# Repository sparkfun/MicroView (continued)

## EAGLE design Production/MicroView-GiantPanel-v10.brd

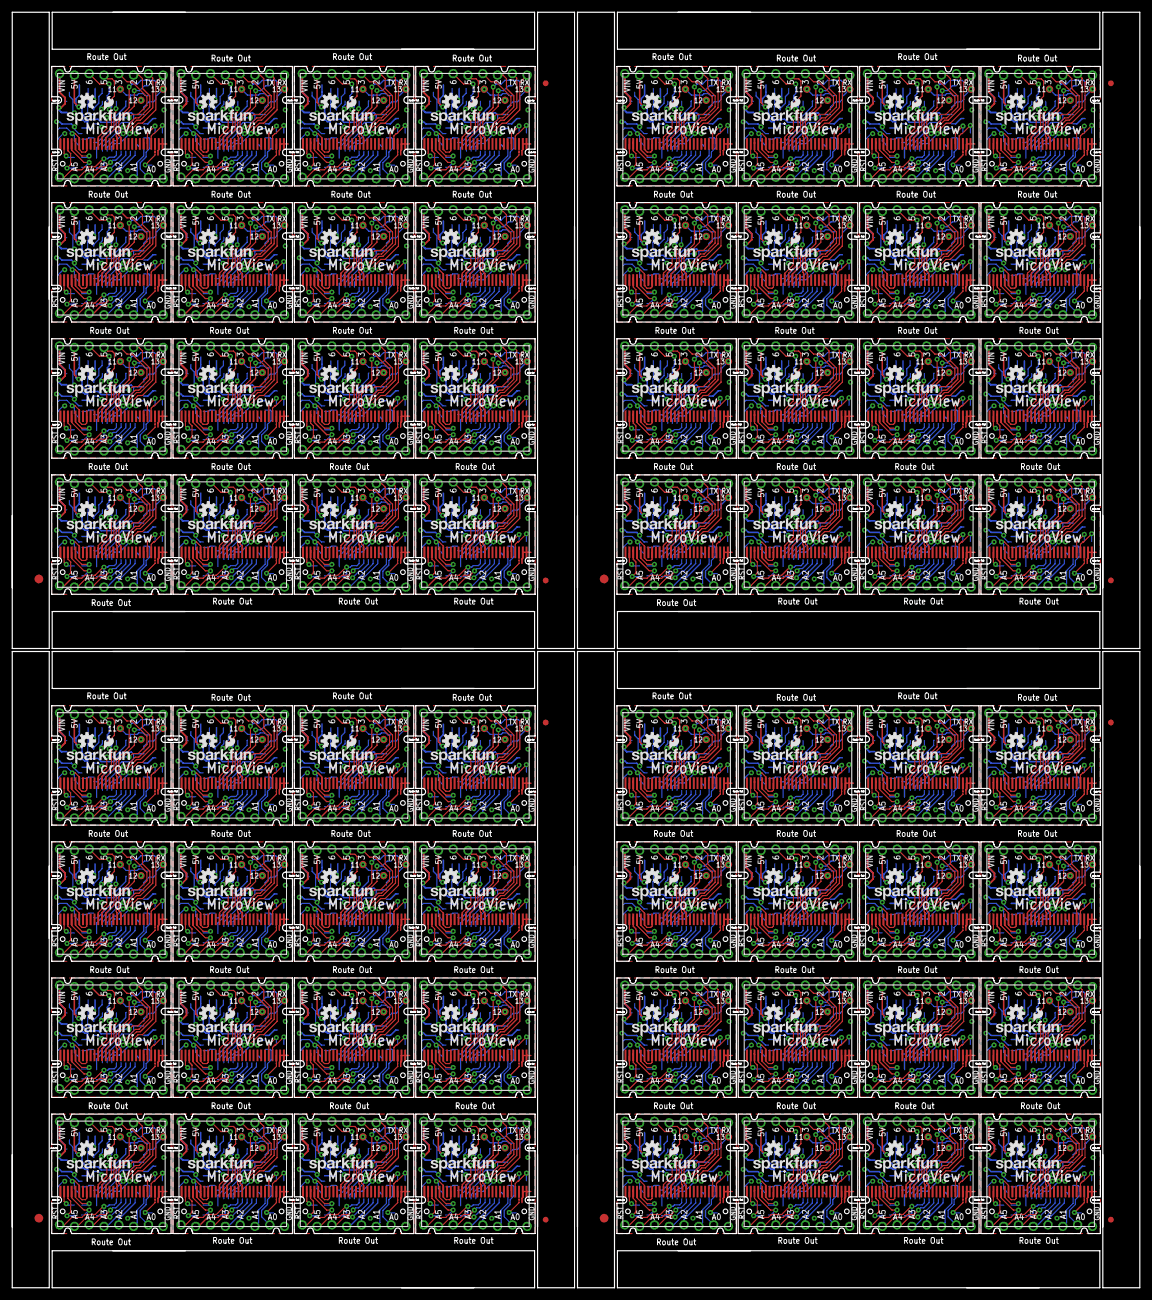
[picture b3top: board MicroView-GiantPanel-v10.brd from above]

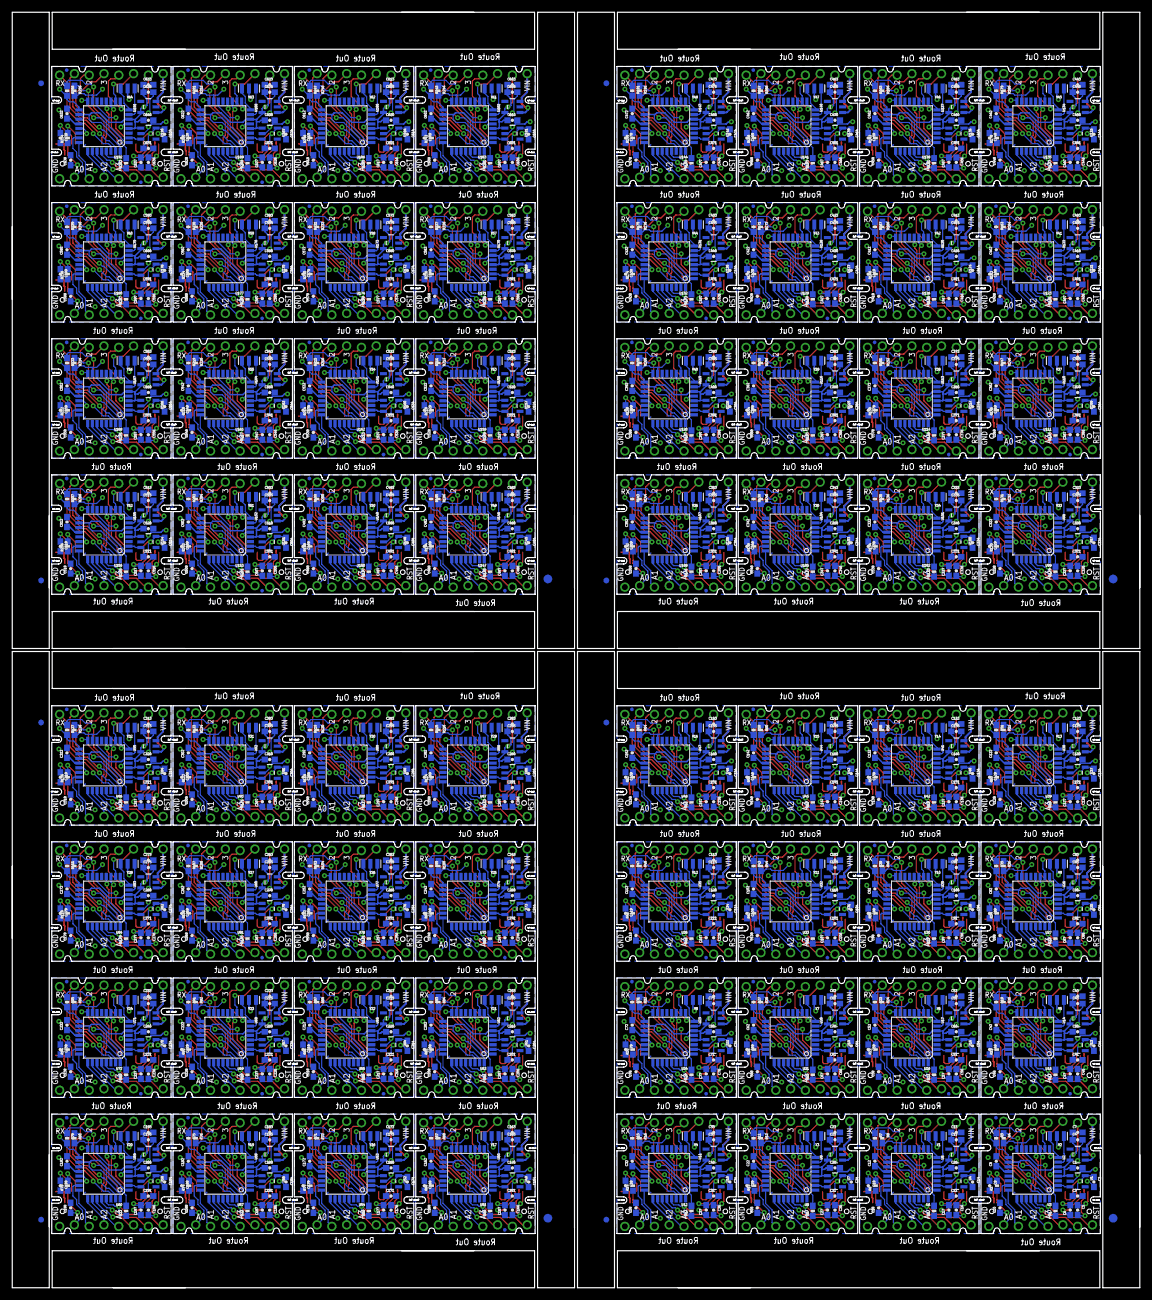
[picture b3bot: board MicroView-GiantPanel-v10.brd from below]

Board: 2 copper layers, 193.5 x 218.9 mm, 1816 parts (1292 on the bottom side), 2304 nets.

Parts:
C1, C2, C4, C5, C6, C14, C15, C16, C17, C20, C24, C25, C26, C27, C30, C34, C35, C36, C37, C40, C44, C45, C46, C47, C50, C54, C55, C56, C57, C60, C64, C65, C66, C67, C70, C74, C75, C76, C77, C80, C84, C85, C86, C87, C90, C94, C95, C96, C97, C100, C104, C105, C106, C107, C110, C114, C115, C116, C117, C120, C124, C125, C126, C127, C130, C134, C135, C136, C137, C140, C144, C145, C146, C147, C150, C154, C155, C156, C157, C160, C164, C165, C166, C167, C170, C174, C175, C176, C177, C180, C184, C185, C186, C187, C190, C194, C195, C196, C197, C200, C204, C205, C206, C207, C210, C214, C215, C216, C217, C220, C224, C225, C226, C227, C230, C234, C235, C236, C237, C240, C244, C245, C246, C247, C250, C254, C255, C256, C257, C260, C264, C265, C266, C267, C270, C274, C275, C276, C277, C280, C284, C285, C286, C287, C290, C294, C295, C296, C297, C300, C304, C305, C306, C307, C310, C314, C315, C316, C317, C320, C324, C325, C326, C327, C330, C334, C335, C336, C337, C340, C344, C345, C346, C347, C350, C354, C355, C356, C357, C360, C364, C365, C366, C367, C370, C374, C375, C376, C377, C380, C384, C385, C386, C387, C390, C394, C395, C396, C397, C400, C404, C405, C406, C407, C410, C414, C415, C416, C417, C420, C424, C425, C426, C427, C430, C434, C435, C436, C437, C440, C444, C445, C446, C447, C450, C454, C455, C456, C457, C460, C464, C465, C466, C467, C470, C474, C475, C476, C477, C480, C484, C485, C486, C487, C490, C494, C495, C496, C497, C500, C504, C505, C506, C507, C510, C514, C515, C516, C517, C520, C524, C525, C526, C527, C530, C534, C535, C536, C537, C540, C544, C545, C546, C547, C550, C554, C555, C556, C557, C560, C564, C565, C566, C567, C570, C574, C575, C576, C577, C580, C584, C585, C586, C587, C590, C594, C595, C596, C597, C600, C604, C605, C606, C607, C610, C614, C615, C616, C617, C620, C624, C625, C626, C627, C630, C634, C635, C636, C637, C640: 1.0uF; 0603-CAP
C3, C7, C8, C11, C12, C13, C21, C22, C23, C31, C32, C33, C41, C42, C43, C51, C52, C53, C61, C62, C63, C71, C72, C73, C81, C82, C83, C91, C92, C93, C101, C102, C103, C111, C112, C113, C121, C122, C123, C131, C132, C133, C141, C142, C143, C151, C152, C153, C161, C162, C163, C171, C172, C173, C181, C182, C183, C191, C192, C193, C201, C202, C203, C211, C212, C213, C221, C222, C223, C231, C232, C233, C241, C242, C243, C251, C252, C253, C261, C262, C263, C271, C272, C273, C281, C282, C283, C291, C292, C293, C301, C302, C303, C311, C312, C313, C321, C322, C323, C331, C332, C333, C341, C342, C343, C351, C352, C353, C361, C362, C363, C371, C372, C373, C381, C382, C383, C391, C392, C393, C401, C402, C403, C411, C412, C413, C421, C422, C423, C431, C432, C433, C441, C442, C443, C451, C452, C453, C461, C462, C463, C471, C472, C473, C481, C482, C483, C491, C492, C493, C501, C502, C503, C511, C512, C513, C521, C522, C523, C531, C532, C533, C541, C542, C543, C551, C552, C553, C561, C562, C563, C571, C572, C573, C581, C582, C583, C591, C592, C593, C601, C602, C603, C611, C612, C613, C621, C622, C623, C631, C632, C633: 0.1uF; 0603-CAP
C9, C10, C18, C19, C28, C29, C38, C39, C48, C49, C58, C59, C68, C69, C78, C79, C88, C89, C98, C99, C108, C109, C118, C119, C128, C129, C138, C139, C148, C149, C158, C159, C168, C169, C178, C179, C188, C189, C198, C199, C208, C209, C218, C219, C228, C229, C238, C239, C248, C249, C258, C259, C268, C269, C278, C279, C288, C289, C298, C299, C308, C309, C318, C319, C328, C329, C338, C339, C348, C349, C358, C359, C368, C369, C378, C379, C388, C389, C398, C399, C408, C409, C418, C419, C428, C429, C438, C439, C448, C449, C458, C459, C468, C469, C478, C479, C488, C489, C498, C499, C508, C509, C518, C519, C528, C529, C538, C539, C548, C549, C558, C559, C568, C569, C578, C579, C588, C589, C598, C599, C608, C609, C618, C619, C628, C629, C638, C639: 2.2uF; 0603-CAP
E$1, E$2, E$9, E$10, E$15, E$16, E$21, E$22: FIDUCIAL-1.5X3
E$3, E$4, E$5, E$6, E$7, E$8, E$11, E$12, E$13, E$14, E$17, E$18, E$19, E$20, E$23, E$24: FIDUCIAL-1X2
FID1, FID2, FID3, FID4, FID5, FID6, FID7, FID8, FID9, FID10, FID11, FID12, FID13, FID14, FID15, FID16, FID17, FID18, FID19, FID20, FID21, FID22, FID23, FID24, FID25, FID26, FID27, FID28, FID29, FID30, FID31, FID32, FID33, FID34, FID35, FID36, FID37, FID38, FID39, FID40, FID41, FID42, FID43, FID44, FID45, FID46, FID47, FID48, FID49, FID50, FID51, FID52, FID53, FID54, FID55, FID56, FID57, FID58, FID59, FID60, FID61, FID62, FID63, FID64, FID65, FID66, FID67, FID68, FID69, FID70, FID71, FID72, FID73, FID74, FID75, FID76, FID77, FID78, FID79, FID80, FID81, FID82, FID83, FID84, FID85, FID86, FID87, FID88, FID89, FID90, FID91, FID92, FID93, FID94, FID95, FID96, FID97, FID98, FID99, FID100, FID101, FID102, FID103, FID104, FID105, FID106, FID107, FID108, FID109, FID110, FID111, FID112, FID113, FID114, FID115, FID116, FID117, FID118, FID119, FID120, FID121, FID122, FID123, FID124, FID125, FID126, FID127, FID128: FIDUCIALUFIDUCIAL; MICRO-FIDUCIAL
J1, J4, J6, J8, J10, J12, J14, J16, J18, J20, J22, J24, J26, J28, J30, J32, J34, J36, J38, J40, J42, J44, J46, J48, J50, J52, J54, J56, J58, J60, J62, J64, J66, J68, J70, J72, J74, J76, J78, J80, J82, J84, J86, J88, J90, J92, J94, J96, J98, J100, J102, J104, J106, J108, J110, J112, J114, J116, J118, J120, J122, J124, J126, J128: OLED_SCREEN; OLED-SCREEN
J2, J3, J5, J7, J9, J11, J13, J15, J17, J19, J21, J23, J25, J27, J29, J31, J33, J35, J37, J39, J41, J43, J45, J47, J49, J51, J53, J55, J57, J59, J61, J63, J65, J67, J69, J71, J73, J75, J77, J79, J81, J83, J85, J87, J89, J91, J93, J95, J97, J99, J101, J103, J105, J107, J109, J111, J113, J115, J117, J119, J121, J123, J125, J127: MICROVIEW-16; MV-DIP16
LOGO1, LOGO2, LOGO5, LOGO7, LOGO9, LOGO11, LOGO13, LOGO15, LOGO17, LOGO19, LOGO21, LOGO23, LOGO25, LOGO27, LOGO29, LOGO31, LOGO33, LOGO35, LOGO37, LOGO39, LOGO41, LOGO43, LOGO45, LOGO47, LOGO49, LOGO51, LOGO53, LOGO55, LOGO57, LOGO59, LOGO61, LOGO63, LOGO65, LOGO67, LOGO69, LOGO71, LOGO73, LOGO75, LOGO77, LOGO79, LOGO81, LOGO83, LOGO85, LOGO87, LOGO89, LOGO91, LOGO93, LOGO95, LOGO97, LOGO99, LOGO101, LOGO103, LOGO105, LOGO107, LOGO109, LOGO111, LOGO113, LOGO115, LOGO117, LOGO119, LOGO121, LOGO123, LOGO125, LOGO127: OSHW-LOGOS; OSHW-LOGO-S
LOGO3, LOGO4, LOGO6, LOGO8, LOGO10, LOGO12, LOGO14, LOGO16, LOGO18, LOGO20, LOGO22, LOGO24, LOGO26, LOGO28, LOGO30, LOGO32, LOGO34, LOGO36, LOGO38, LOGO40, LOGO42, LOGO44, LOGO46, LOGO48, LOGO50, LOGO52, LOGO54, LOGO56, LOGO58, LOGO60, LOGO62, LOGO64, LOGO66, LOGO68, LOGO70, LOGO72, LOGO74, LOGO76, LOGO78, LOGO80, LOGO82, LOGO84, LOGO86, LOGO88, LOGO90, LOGO92, LOGO94, LOGO96, LOGO98, LOGO100, LOGO102, LOGO104, LOGO106, LOGO108, LOGO110, LOGO112, LOGO114, LOGO116, LOGO118, LOGO120, LOGO122, LOGO124, LOGO126, LOGO128: SFE_LOGO_NAME_FLAME.1_INCH; SFE_LOGO_NAME_FLAME_.1
OLED1, OLED2, OLED3, OLED4, OLED5, OLED6, OLED7, OLED8, OLED9, OLED10, OLED11, OLED12, OLED13, OLED14, OLED15, OLED16, OLED17, OLED18, OLED19, OLED20, OLED21, OLED22, OLED23, OLED24, OLED25, OLED26, OLED27, OLED28, OLED29, OLED30, OLED31, OLED32, OLED33, OLED34, OLED35, OLED36, OLED37, OLED38, OLED39, OLED40, OLED41, OLED42, OLED43, OLED44, OLED45, OLED46, OLED47, OLED48, OLED49, OLED50, OLED51, OLED52, OLED53, OLED54, OLED55, OLED56, OLED57, OLED58, OLED59, OLED60, OLED61, OLED62, OLED63, OLED64: OLED0.66; OLED-0.66-64X48
R1, R5, R9, R13, R17, R21, R25, R29, R33, R37, R41, R45, R49, R53, R57, R61, R65, R69, R73, R77, R81, R85, R89, R93, R97, R101, R105, R109, R113, R117, R121, R125, R129, R133, R137, R141, R145, R149, R153, R157, R161, R165, R169, R173, R177, R181, R185, R189, R193, R197, R201, R205, R209, R213, R217, R221, R225, R229, R233, R237, R241, R245, R249, R253: 10K; 0603-RES
R2, R6, R10, R14, R18, R22, R26, R30, R34, R38, R42, R46, R50, R54, R58, R62, R66, R70, R74, R78, R82, R86, R90, R94, R98, R102, R106, R110, R114, R118, R122, R126, R130, R134, R138, R142, R146, R150, R154, R158, R162, R166, R170, R174, R178, R182, R186, R190, R194, R198, R202, R206, R210, R214, R218, R222, R226, R230, R234, R238, R242, R246, R250, R254: 390k; 0603-RES
R3, R4, R7, R8, R11, R12, R15, R16, R19, R20, R23, R24, R27, R28, R31, R32, R35, R36, R39, R40, R43, R44, R47, R48, R51, R52, R55, R56, R59, R60, R63, R64, R67, R68, R71, R72, R75, R76, R79, R80, R83, R84, R87, R88, R91, R92, R95, R96, R99, R100, R103, R104, R107, R108, R111, R112, R115, R116, R119, R120, R123, R124, R127, R128, R131, R132, R135, R136, R139, R140, R143, R144, R147, R148, R151, R152, R155, R156, R159, R160, R163, R164, R167, R168, R171, R172, R175, R176, R179, R180, R183, R184, R187, R188, R191, R192, R195, R196, R199, R200, R203, R204, R207, R208, R211, R212, R215, R216, R219, R220, R223, R224, R227, R228, R231, R232, R235, R236, R239, R240, R243, R244, R247, R248, R251, R252, R255, R256: 1k; 0603-RES
TP1, TP2, TP3, TP4, TP5, TP6, TP7, TP8, TP9, TP10, TP11, TP12, TP13, TP14, TP15, TP16, TP17, TP18, TP19, TP20, TP21, TP22, TP23, TP24, TP25, TP26, TP27, TP28, TP29, TP30, TP31, TP32, TP33, TP34, TP35, TP36, TP37, TP38, TP39, TP40, TP41, TP42, TP43, TP44, TP45, TP46, TP47, TP48, TP49, TP50, TP51, TP52, TP53, TP54, TP55, TP56, TP57, TP58, TP59, TP60, TP61, TP62, TP63, TP64, TP65, TP66, TP67, TP68, TP69, TP70, TP71, TP72, TP73, TP74, TP75, TP76, TP77, TP78, TP79, TP80, TP81, TP82, TP83, TP84, TP85, TP86, TP87, TP88, TP89, TP90, TP91, TP92, TP93, TP94, TP95, TP96, TP97, TP98, TP99, TP100, TP101, TP102, TP103, TP104, TP105, TP106, TP107, TP108, TP109, TP110, TP111, TP112, TP113, TP114, TP115, TP116, TP117, TP118, TP119, TP120, TP121, TP122, TP123, TP124, TP125, TP126, TP127, TP128, TP129, TP130, TP131, TP132, TP133, TP134, TP135, TP136, TP137, TP138, TP139, TP140, TP141, TP142, TP143, TP144, TP145, TP146, TP147, TP148, TP149, TP150, TP151, TP152, TP153, TP154, TP155, TP156, TP157, TP158, TP159, TP160, TP161, TP162, TP163, TP164, TP165, TP166, TP167, TP168, TP169, TP170, TP171, TP172, TP173, TP174, TP175, TP176, TP177, TP178, TP179, TP180, TP181, TP182, TP183, TP184, TP185, TP186, TP187, TP188, TP189, TP190, TP191, TP192: PAD.03X.05
U1, U4, U7, U10, U13, U16, U19, U22, U25, U28, U31, U34, U37, U40, U43, U46, U49, U52, U55, U58, U61, U64, U67, U70, U73, U76, U79, U82, U85, U88, U91, U94, U97, U100, U103, U106, U109, U112, U115, U118, U121, U124, U127, U130, U133, U136, U139, U142, U145, U148, U151, U154, U157, U160, U163, U166, U169, U172, U175, U178, U181, U184, U187, U190: MIC5205 3.3V; SOT23-5
U2, U5, U8, U11, U14, U17, U20, U23, U26, U29, U32, U35, U38, U41, U44, U47, U50, U53, U56, U59, U62, U65, U68, U71, U74, U77, U80, U83, U86, U89, U92, U95, U98, U101, U104, U107, U110, U113, U116, U119, U122, U125, U128, U131, U134, U137, U140, U143, U146, U149, U152, U155, U158, U161, U164, U167, U170, U173, U176, U179, U182, U185, U188, U191: SPX3819M5-L-5-0; SOT23-5
U3, U6, U9, U12, U15, U18, U21, U24, U27, U30, U33, U36, U39, U42, U45, U48, U51, U54, U57, U60, U63, U66, U69, U72, U75, U78, U81, U84, U87, U90, U93, U96, U99, U102, U105, U108, U111, U114, U117, U120, U123, U126, U129, U132, U135, U138, U141, U144, U147, U150, U153, U156, U159, U162, U165, U168, U171, U174, U177, U180, U183, U186, U189, U192: ATMEGA328P; TQFP32-08
Y1, Y2, Y3, Y4, Y5, Y6, Y7, Y8, Y9, Y10, Y11, Y12, Y13, Y14, Y15, Y16, Y17, Y18, Y19, Y20, Y21, Y22, Y23, Y24, Y25, Y26, Y27, Y28, Y29, Y30, Y31, Y32, Y33, Y34, Y35, Y36, Y37, Y38, Y39, Y40, Y41, Y42, Y43, Y44, Y45, Y46, Y47, Y48, Y49, Y50, Y51, Y52, Y53, Y54, Y55, Y56, Y57, Y58, Y59, Y60, Y61, Y62, Y63, Y64: 16MHz; RESONATOR-SMD

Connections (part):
3.3V: C2.1, C3.1, OLED1.6, OLED1.8, U1.5
3.3V1: C11.1, C14.1, OLED2.6, OLED2.8, U4.5
3.3V2: C21.1, C24.1, OLED3.6, OLED3.8, U7.5
3.3V3: C31.1, C34.1, OLED4.6, OLED4.8, U10.5
3.3V4: C41.1, C44.1, OLED5.6, OLED5.8, U13.5
3.3V5: C51.1, C54.1, OLED6.6, OLED6.8, U16.5
3.3V6: C61.1, C64.1, OLED7.6, OLED7.8, U19.5
3.3V7: C71.1, C74.1, OLED8.6, OLED8.8, U22.5
3.3V8: C81.1, C84.1, OLED9.6, OLED9.8, U25.5
3.3V9: C91.1, C94.1, OLED10.6, OLED10.8, U28.5
3.3V10: C101.1, C104.1, OLED11.6, OLED11.8, U31.5
3.3V11: C111.1, C114.1, OLED12.6, OLED12.8, U34.5
3.3V12: C121.1, C124.1, OLED13.6, OLED13.8, U37.5
3.3V13: C131.1, C134.1, OLED14.6, OLED14.8, U40.5
3.3V14: C141.1, C144.1, OLED15.6, OLED15.8, U43.5
3.3V15: C151.1, C154.1, OLED16.6, OLED16.8, U46.5
3.3V16: C161.1, C164.1, OLED17.6, OLED17.8, U49.5
3.3V17: C171.1, C174.1, OLED18.6, OLED18.8, U52.5
3.3V18: C181.1, C184.1, OLED19.6, OLED19.8, U55.5
3.3V19: C191.1, C194.1, OLED20.6, OLED20.8, U58.5
3.3V20: C201.1, C204.1, OLED21.6, OLED21.8, U61.5
3.3V21: C211.1, C214.1, OLED22.6, OLED22.8, U64.5
3.3V22: C221.1, C224.1, OLED23.6, OLED23.8, U67.5
3.3V23: C231.1, C234.1, OLED24.6, OLED24.8, U70.5
3.3V24: C241.1, C244.1, OLED25.6, OLED25.8, U73.5
3.3V25: C251.1, C254.1, OLED26.6, OLED26.8, U76.5
3.3V26: C261.1, C264.1, OLED27.6, OLED27.8, U79.5
3.3V27: C271.1, C274.1, OLED28.6, OLED28.8, U82.5
3.3V28: C281.1, C284.1, OLED29.6, OLED29.8, U85.5
3.3V29: C291.1, C294.1, OLED30.6, OLED30.8, U88.5
3.3V30: C301.1, C304.1, OLED31.6, OLED31.8, U91.5
3.3V31: C311.1, C314.1, OLED32.6, OLED32.8, U94.5
3.3V32: C321.1, C324.1, OLED33.6, OLED33.8, U97.5
3.3V33: C331.1, C334.1, OLED34.6, OLED34.8, U100.5
3.3V34: C341.1, C344.1, OLED35.6, OLED35.8, U103.5
3.3V35: C351.1, C354.1, OLED36.6, OLED36.8, U106.5
3.3V36: C361.1, C364.1, OLED37.6, OLED37.8, U109.5
3.3V37: C371.1, C374.1, OLED38.6, OLED38.8, U112.5
3.3V38: C381.1, C384.1, OLED39.6, OLED39.8, U115.5
3.3V39: C391.1, C394.1, OLED40.6, OLED40.8, U118.5
3.3V40: C401.1, C404.1, OLED41.6, OLED41.8, U121.5
3.3V41: C411.1, C414.1, OLED42.6, OLED42.8, U124.5
3.3V42: C421.1, C424.1, OLED43.6, OLED43.8, U127.5
3.3V43: C431.1, C434.1, OLED44.6, OLED44.8, U130.5
3.3V44: C441.1, C444.1, OLED45.6, OLED45.8, U133.5
3.3V45: C451.1, C454.1, OLED46.6, OLED46.8, U136.5
3.3V46: C461.1, C464.1, OLED47.6, OLED47.8, U139.5
3.3V47: C471.1, C474.1, OLED48.6, OLED48.8, U142.5
3.3V48: C481.1, C484.1, OLED49.6, OLED49.8, U145.5
3.3V49: C491.1, C494.1, OLED50.6, OLED50.8, U148.5
3.3V50: C501.1, C504.1, OLED51.6, OLED51.8, U151.5
3.3V51: C511.1, C514.1, OLED52.6, OLED52.8, U154.5
3.3V52: C521.1, C524.1, OLED53.6, OLED53.8, U157.5
3.3V53: C531.1, C534.1, OLED54.6, OLED54.8, U160.5
3.3V54: C541.1, C544.1, OLED55.6, OLED55.8, U163.5
3.3V55: C551.1, C554.1, OLED56.6, OLED56.8, U166.5
3.3V56: C561.1, C564.1, OLED57.6, OLED57.8, U169.5
3.3V57: C571.1, C574.1, OLED58.6, OLED58.8, U172.5
3.3V58: C581.1, C584.1, OLED59.6, OLED59.8, U175.5
3.3V59: C591.1, C594.1, OLED60.6, OLED60.8, U178.5
3.3V60: C601.1, C604.1, OLED61.6, OLED61.8, U181.5
3.3V61: C611.1, C614.1, OLED62.6, OLED62.8, U184.5
3.3V62: C621.1, C624.1, OLED63.6, OLED63.8, U187.5
3.3V63: C631.1, C634.1, OLED64.6, OLED64.8, U190.5
5V: C1.1, C4.1, C7.1, J2.15, R1.2, U1.1, U2.5, U3.4, U3.6, U3.18
5V1: C13.1, C15.1, C20.1, J3.15, R5.2, U4.1, U5.5, U6.4, U6.6, U6.18
5V2: C23.1, C25.1, C30.1, J5.15, R9.2, U7.1, U8.5, U9.4, U9.6, U9.18
5V3: C33.1, C35.1, C40.1, J7.15, R13.2, U10.1, U11.5, U12.4, U12.6, U12.18
5V4: C43.1, C45.1, C50.1, J9.15, R17.2, U13.1, U14.5, U15.4, U15.6, U15.18
5V5: C53.1, C55.1, C60.1, J11.15, R21.2, U16.1, U17.5, U18.4, U18.6, U18.18
5V6: C63.1, C65.1, C70.1, J13.15, R25.2, U19.1, U20.5, U21.4, U21.6, U21.18
5V7: C73.1, C75.1, C80.1, J15.15, R29.2, U22.1, U23.5, U24.4, U24.6, U24.18
5V8: C83.1, C85.1, C90.1, J17.15, R33.2, U25.1, U26.5, U27.4, U27.6, U27.18
5V9: C93.1, C95.1, C100.1, J19.15, R37.2, U28.1, U29.5, U30.4, U30.6, U30.18
5V10: C103.1, C105.1, C110.1, J21.15, R41.2, U31.1, U32.5, U33.4, U33.6, U33.18
5V11: C113.1, C115.1, C120.1, J23.15, R45.2, U34.1, U35.5, U36.4, U36.6, U36.18
5V12: C123.1, C125.1, C130.1, J25.15, R49.2, U37.1, U38.5, U39.4, U39.6, U39.18
5V13: C133.1, C135.1, C140.1, J27.15, R53.2, U40.1, U41.5, U42.4, U42.6, U42.18
5V14: C143.1, C145.1, C150.1, J29.15, R57.2, U43.1, U44.5, U45.4, U45.6, U45.18
5V15: C153.1, C155.1, C160.1, J31.15, R61.2, U46.1, U47.5, U48.4, U48.6, U48.18
5V16: C163.1, C165.1, C170.1, J33.15, R65.2, U49.1, U50.5, U51.4, U51.6, U51.18
5V17: C173.1, C175.1, C180.1, J35.15, R69.2, U52.1, U53.5, U54.4, U54.6, U54.18
5V18: C183.1, C185.1, C190.1, J37.15, R73.2, U55.1, U56.5, U57.4, U57.6, U57.18
5V19: C193.1, C195.1, C200.1, J39.15, R77.2, U58.1, U59.5, U60.4, U60.6, U60.18
5V20: C203.1, C205.1, C210.1, J41.15, R81.2, U61.1, U62.5, U63.4, U63.6, U63.18
5V21: C213.1, C215.1, C220.1, J43.15, R85.2, U64.1, U65.5, U66.4, U66.6, U66.18
5V22: C223.1, C225.1, C230.1, J45.15, R89.2, U67.1, U68.5, U69.4, U69.6, U69.18
5V23: C233.1, C235.1, C240.1, J47.15, R93.2, U70.1, U71.5, U72.4, U72.6, U72.18
5V24: C243.1, C245.1, C250.1, J49.15, R97.2, U73.1, U74.5, U75.4, U75.6, U75.18
5V25: C253.1, C255.1, C260.1, J51.15, R101.2, U76.1, U77.5, U78.4, U78.6, U78.18
5V26: C263.1, C265.1, C270.1, J53.15, R105.2, U79.1, U80.5, U81.4, U81.6, U81.18
5V27: C273.1, C275.1, C280.1, J55.15, R109.2, U82.1, U83.5, U84.4, U84.6, U84.18
5V28: C283.1, C285.1, C290.1, J57.15, R113.2, U85.1, U86.5, U87.4, U87.6, U87.18
5V29: C293.1, C295.1, C300.1, J59.15, R117.2, U88.1, U89.5, U90.4, U90.6, U90.18
5V30: C303.1, C305.1, C310.1, J61.15, R121.2, U91.1, U92.5, U93.4, U93.6, U93.18
5V31: C313.1, C315.1, C320.1, J63.15, R125.2, U94.1, U95.5, U96.4, U96.6, U96.18
5V32: C323.1, C325.1, C330.1, J65.15, R129.2, U97.1, U98.5, U99.4, U99.6, U99.18
5V33: C333.1, C335.1, C340.1, J67.15, R133.2, U100.1, U101.5, U102.4, U102.6, U102.18
5V34: C343.1, C345.1, C350.1, J69.15, R137.2, U103.1, U104.5, U105.4, U105.6, U105.18
5V35: C353.1, C355.1, C360.1, J71.15, R141.2, U106.1, U107.5, U108.4, U108.6, U108.18
5V36: C363.1, C365.1, C370.1, J73.15, R145.2, U109.1, U110.5, U111.4, U111.6, U111.18
5V37: C373.1, C375.1, C380.1, J75.15, R149.2, U112.1, U113.5, U114.4, U114.6, U114.18
5V38: C383.1, C385.1, C390.1, J77.15, R153.2, U115.1, U116.5, U117.4, U117.6, U117.18
5V39: C393.1, C395.1, C400.1, J79.15, R157.2, U118.1, U119.5, U120.4, U120.6, U120.18
5V40: C403.1, C405.1, C410.1, J81.15, R161.2, U121.1, U122.5, U123.4, U123.6, U123.18
5V41: C413.1, C415.1, C420.1, J83.15, R165.2, U124.1, U125.5, U126.4, U126.6, U126.18
5V42: C423.1, C425.1, C430.1, J85.15, R169.2, U127.1, U128.5, U129.4, U129.6, U129.18
5V43: C433.1, C435.1, C440.1, J87.15, R173.2, U130.1, U131.5, U132.4, U132.6, U132.18
5V44: C443.1, C445.1, C450.1, J89.15, R177.2, U133.1, U134.5, U135.4, U135.6, U135.18
5V45: C453.1, C455.1, C460.1, J91.15, R181.2, U136.1, U137.5, U138.4, U138.6, U138.18
5V46: C463.1, C465.1, C470.1, J93.15, R185.2, U139.1, U140.5, U141.4, U141.6, U141.18
5V47: C473.1, C475.1, C480.1, J95.15, R189.2, U142.1, U143.5, U144.4, U144.6, U144.18
5V48: C483.1, C485.1, C490.1, J97.15, R193.2, U145.1, U146.5, U147.4, U147.6, U147.18
5V49: C493.1, C495.1, C500.1, J99.15, R197.2, U148.1, U149.5, U150.4, U150.6, U150.18
5V50: C503.1, C505.1, C510.1, J101.15, R201.2, U151.1, U152.5, U153.4, U153.6, U153.18
5V51: C513.1, C515.1, C520.1, J103.15, R205.2, U154.1, U155.5, U156.4, U156.6, U156.18
5V52: C523.1, C525.1, C530.1, J105.15, R209.2, U157.1, U158.5, U159.4, U159.6, U159.18
5V53: C533.1, C535.1, C540.1, J107.15, R213.2, U160.1, U161.5, U162.4, U162.6, U162.18
5V54: C543.1, C545.1, C550.1, J109.15, R217.2, U163.1, U164.5, U165.4, U165.6, U165.18
5V55: C553.1, C555.1, C560.1, J111.15, R221.2, U166.1, U167.5, U168.4, U168.6, U168.18
5V56: C563.1, C565.1, C570.1, J113.15, R225.2, U169.1, U170.5, U171.4, U171.6, U171.18
5V57: C573.1, C575.1, C580.1, J115.15, R229.2, U172.1, U173.5, U174.4, U174.6, U174.18
5V58: C583.1, C585.1, C590.1, J117.15, R233.2, U175.1, U176.5, U177.4, U177.6, U177.18
5V59: C593.1, C595.1, C600.1, J119.15, R237.2, U178.1, U179.5, U180.4, U180.6, U180.18
5V60: C603.1, C605.1, C610.1, J121.15, R241.2, U181.1, U182.5, U183.4, U183.6, U183.18
5V61: C613.1, C615.1, C620.1, J123.15, R245.2, U184.1, U185.5, U186.4, U186.6, U186.18
5V62: C623.1, C625.1, C630.1, J125.15, R249.2, U187.1, U188.5, U189.4, U189.6, U189.18
5V63: C633.1, C635.1, C640.1, J127.15, R253.2, U190.1, U191.5, U192.4, U192.6, U192.18
A0: J2.7, U3.23
A1: J2.6, U3.24
A2: J2.5, U3.25
A3: J2.4, U3.26
A4: J2.3, U3.27
A5: J2.2, U3.28
A6: J3.7, U6.23
A7: J3.6, U6.24
A8: J3.5, U6.25
A9: J3.4, U6.26
A10: J3.3, U6.27
A11: J3.2, U6.28
A12: J5.7, U9.23
A13: J5.6, U9.24
A14: J5.5, U9.25
A15: J5.4, U9.26
A16: J5.3, U9.27
A17: J5.2, U9.28
A18: J7.7, U12.23
A19: J7.6, U12.24
A20: J7.5, U12.25
A21: J7.4, U12.26
A22: J7.3, U12.27
A23: J7.2, U12.28
A24: J9.7, U15.23
A25: J9.6, U15.24
A26: J9.5, U15.25
A27: J9.4, U15.26
A28: J9.3, U15.27
A29: J9.2, U15.28
A30: J11.7, U18.23
A31: J11.6, U18.24
A32: J11.5, U18.25
A33: J11.4, U18.26
A34: J11.3, U18.27
A35: J11.2, U18.28
A36: J13.7, U21.23
A37: J13.6, U21.24
A38: J13.5, U21.25
A39: J13.4, U21.26
A40: J13.3, U21.27
A41: J13.2, U21.28
A42: J15.7, U24.23
A43: J15.6, U24.24
A44: J15.5, U24.25
A45: J15.4, U24.26
A46: J15.3, U24.27
A47: J15.2, U24.28
A48: J17.7, U27.23
A49: J17.6, U27.24
A50: J17.5, U27.25
A51: J17.4, U27.26
A52: J17.3, U27.27
A53: J17.2, U27.28
A54: J19.7, U30.23
A55: J19.6, U30.24
A56: J19.5, U30.25
A57: J19.4, U30.26
A58: J19.3, U30.27
A59: J19.2, U30.28
A60: J21.7, U33.23
A61: J21.6, U33.24
A62: J21.5, U33.25
A63: J21.4, U33.26
A64: J21.3, U33.27
A65: J21.2, U33.28
A66: J23.7, U36.23
A67: J23.6, U36.24
A68: J23.5, U36.25
A69: J23.4, U36.26
A70: J23.3, U36.27
A71: J23.2, U36.28
A72: J25.7, U39.23
A73: J25.6, U39.24
A74: J25.5, U39.25
A75: J25.4, U39.26
A76: J25.3, U39.27
A77: J25.2, U39.28
A78: J27.7, U42.23
A79: J27.6, U42.24
A80: J27.5, U42.25
A81: J27.4, U42.26
A82: J27.3, U42.27
A83: J27.2, U42.28
A84: J29.7, U45.23
A85: J29.6, U45.24
A86: J29.5, U45.25
A87: J29.4, U45.26
A88: J29.3, U45.27
A89: J29.2, U45.28
A90: J31.7, U48.23
A91: J31.6, U48.24
A92: J31.5, U48.25
A93: J31.4, U48.26
A94: J31.3, U48.27
A95: J31.2, U48.28
A96: J33.7, U51.23
A97: J33.6, U51.24
A98: J33.5, U51.25
A99: J33.4, U51.26
A100: J33.3, U51.27
A101: J33.2, U51.28
A102: J35.7, U54.23
A103: J35.6, U54.24
A104: J35.5, U54.25
A105: J35.4, U54.26
A106: J35.3, U54.27
A107: J35.2, U54.28
A108: J37.7, U57.23
A109: J37.6, U57.24
A110: J37.5, U57.25
A111: J37.4, U57.26
A112: J37.3, U57.27
A113: J37.2, U57.28
A114: J39.7, U60.23
A115: J39.6, U60.24
A116: J39.5, U60.25
A117: J39.4, U60.26
A118: J39.3, U60.27
A119: J39.2, U60.28
A120: J41.7, U63.23
A121: J41.6, U63.24
A122: J41.5, U63.25
A123: J41.4, U63.26
A124: J41.3, U63.27
A125: J41.2, U63.28
A126: J43.7, U66.23
A127: J43.6, U66.24
A128: J43.5, U66.25
A129: J43.4, U66.26
A130: J43.3, U66.27
A131: J43.2, U66.28
A132: J45.7, U69.23
A133: J45.6, U69.24
A134: J45.5, U69.25
A135: J45.4, U69.26
A136: J45.3, U69.27
A137: J45.2, U69.28
A138: J47.7, U72.23
A139: J47.6, U72.24
A140: J47.5, U72.25
A141: J47.4, U72.26
A142: J47.3, U72.27
A143: J47.2, U72.28
A144: J49.7, U75.23
A145: J49.6, U75.24
A146: J49.5, U75.25
A147: J49.4, U75.26
A148: J49.3, U75.27
A149: J49.2, U75.28
A150: J51.7, U78.23
A151: J51.6, U78.24
A152: J51.5, U78.25
A153: J51.4, U78.26
A154: J51.3, U78.27
A155: J51.2, U78.28
A156: J53.7, U81.23
A157: J53.6, U81.24
A158: J53.5, U81.25
A159: J53.4, U81.26
A160: J53.3, U81.27
A161: J53.2, U81.28
A162: J55.7, U84.23
A163: J55.6, U84.24
A164: J55.5, U84.25
A165: J55.4, U84.26
A166: J55.3, U84.27
A167: J55.2, U84.28
A168: J57.7, U87.23
A169: J57.6, U87.24
A170: J57.5, U87.25
A171: J57.4, U87.26
A172: J57.3, U87.27
A173: J57.2, U87.28
A174: J59.7, U90.23
A175: J59.6, U90.24
A176: J59.5, U90.25
A177: J59.4, U90.26
A178: J59.3, U90.27
A179: J59.2, U90.28
A180: J61.7, U93.23
A181: J61.6, U93.24
A182: J61.5, U93.25
A183: J61.4, U93.26
A184: J61.3, U93.27
A185: J61.2, U93.28
A186: J63.7, U96.23
A187: J63.6, U96.24
A188: J63.5, U96.25
A189: J63.4, U96.26
A190: J63.3, U96.27
A191: J63.2, U96.28
A192: J65.7, U99.23
A193: J65.6, U99.24
A194: J65.5, U99.25
A195: J65.4, U99.26
A196: J65.3, U99.27
A197: J65.2, U99.28
A198: J67.7, U102.23
A199: J67.6, U102.24
A200: J67.5, U102.25
A201: J67.4, U102.26
A202: J67.3, U102.27
A203: J67.2, U102.28
A204: J69.7, U105.23
A205: J69.6, U105.24
A206: J69.5, U105.25
A207: J69.4, U105.26
A208: J69.3, U105.27
A209: J69.2, U105.28
A210: J71.7, U108.23
A211: J71.6, U108.24
A212: J71.5, U108.25
A213: J71.4, U108.26
A214: J71.3, U108.27
A215: J71.2, U108.28
A216: J73.7, U111.23
A217: J73.6, U111.24
A218: J73.5, U111.25
A219: J73.4, U111.26
A220: J73.3, U111.27
A221: J73.2, U111.28
A222: J75.7, U114.23
A223: J75.6, U114.24
A224: J75.5, U114.25
A225: J75.4, U114.26
A226: J75.3, U114.27
A227: J75.2, U114.28
A228: J77.7, U117.23
A229: J77.6, U117.24
A230: J77.5, U117.25
A231: J77.4, U117.26
A232: J77.3, U117.27
A233: J77.2, U117.28
A234: J79.7, U120.23
A235: J79.6, U120.24
A236: J79.5, U120.25
A237: J79.4, U120.26
A238: J79.3, U120.27
A239: J79.2, U120.28
A240: J81.7, U123.23
A241: J81.6, U123.24
A242: J81.5, U123.25
A243: J81.4, U123.26
A244: J81.3, U123.27
A245: J81.2, U123.28
A246: J83.7, U126.23
A247: J83.6, U126.24
A248: J83.5, U126.25
A249: J83.4, U126.26
A250: J83.3, U126.27
A251: J83.2, U126.28
A252: J85.7, U129.23
A253: J85.6, U129.24
A254: J85.5, U129.25
A255: J85.4, U129.26
A256: J85.3, U129.27
A257: J85.2, U129.28
A258: J87.7, U132.23
A259: J87.6, U132.24
A260: J87.5, U132.25
A261: J87.4, U132.26
A262: J87.3, U132.27
A263: J87.2, U132.28
A264: J89.7, U135.23
A265: J89.6, U135.24
A266: J89.5, U135.25
A267: J89.4, U135.26
A268: J89.3, U135.27
A269: J89.2, U135.28
A270: J91.7, U138.23
A271: J91.6, U138.24
A272: J91.5, U138.25
A273: J91.4, U138.26
A274: J91.3, U138.27
A275: J91.2, U138.28
A276: J93.7, U141.23
A277: J93.6, U141.24
A278: J93.5, U141.25
A279: J93.4, U141.26
A280: J93.3, U141.27
A281: J93.2, U141.28
A282: J95.7, U144.23
A283: J95.6, U144.24
A284: J95.5, U144.25
A285: J95.4, U144.26
A286: J95.3, U144.27
A287: J95.2, U144.28
A288: J97.7, U147.23
A289: J97.6, U147.24
A290: J97.5, U147.25
A291: J97.4, U147.26
A292: J97.3, U147.27
A293: J97.2, U147.28
A294: J99.7, U150.23
A295: J99.6, U150.24
A296: J99.5, U150.25
A297: J99.4, U150.26
A298: J99.3, U150.27
A299: J99.2, U150.28
A300: J101.7, U153.23
A301: J101.6, U153.24
A302: J101.5, U153.25
A303: J101.4, U153.26
A304: J101.3, U153.27
A305: J101.2, U153.28
A306: J103.7, U156.23
A307: J103.6, U156.24
A308: J103.5, U156.25
A309: J103.4, U156.26
A310: J103.3, U156.27
A311: J103.2, U156.28
A312: J105.7, U159.23
A313: J105.6, U159.24
A314: J105.5, U159.25
A315: J105.4, U159.26
A316: J105.3, U159.27
A317: J105.2, U159.28
A318: J107.7, U162.23
A319: J107.6, U162.24
A320: J107.5, U162.25
A321: J107.4, U162.26
A322: J107.3, U162.27
A323: J107.2, U162.28
A324: J109.7, U165.23
A325: J109.6, U165.24
A326: J109.5, U165.25
A327: J109.4, U165.26
A328: J109.3, U165.27
A329: J109.2, U165.28
A330: J111.7, U168.23
A331: J111.6, U168.24
A332: J111.5, U168.25
A333: J111.4, U168.26
A334: J111.3, U168.27
A335: J111.2, U168.28
A336: J113.7, U171.23
A337: J113.6, U171.24
A338: J113.5, U171.25
A339: J113.4, U171.26
A340: J113.3, U171.27
A341: J113.2, U171.28
A342: J115.7, U174.23
A343: J115.6, U174.24
A344: J115.5, U174.25
A345: J115.4, U174.26
A346: J115.3, U174.27
A347: J115.2, U174.28
A348: J117.7, U177.23
A349: J117.6, U177.24
A350: J117.5, U177.25
A351: J117.4, U177.26
A352: J117.3, U177.27
A353: J117.2, U177.28
A354: J119.7, U180.23
A355: J119.6, U180.24
A356: J119.5, U180.25
A357: J119.4, U180.26
A358: J119.3, U180.27
A359: J119.2, U180.28
A360: J121.7, U183.23
A361: J121.6, U183.24
A362: J121.5, U183.25
A363: J121.4, U183.26
A364: J121.3, U183.27
A365: J121.2, U183.28
A366: J123.7, U186.23
A367: J123.6, U186.24
A368: J123.5, U186.25
A369: J123.4, U186.26
A370: J123.3, U186.27
A371: J123.2, U186.28
A372: J125.7, U189.23
A373: J125.6, U189.24
A374: J125.5, U189.25
A375: J125.4, U189.26
A376: J125.3, U189.27
A377: J125.2, U189.28
A378: J127.7, U192.23
A379: J127.6, U192.24
A380: J127.5, U192.25
A381: J127.4, U192.26
A382: J127.3, U192.27
A383: J127.2, U192.28
C1N: C6.2, OLED1.5
C1N1: C17.2, OLED2.5
C1N2: C27.2, OLED3.5
C1N3: C37.2, OLED4.5
C1N4: C47.2, OLED5.5
C1N5: C57.2, OLED6.5
C1N6: C67.2, OLED7.5
C1N7: C77.2, OLED8.5
C1N8: C87.2, OLED9.5
C1N9: C97.2, OLED10.5
C1N10: C107.2, OLED11.5
C1N11: C117.2, OLED12.5
C1N12: C127.2, OLED13.5
C1N13: C137.2, OLED14.5
C1N14: C147.2, OLED15.5
C1N15: C157.2, OLED16.5
C1N16: C167.2, OLED17.5
C1N17: C177.2, OLED18.5
C1N18: C187.2, OLED19.5
C1N19: C197.2, OLED20.5
C1N20: C207.2, OLED21.5
C1N21: C217.2, OLED22.5
C1N22: C227.2, OLED23.5
C1N23: C237.2, OLED24.5
C1N24: C247.2, OLED25.5
C1N25: C257.2, OLED26.5
C1N26: C267.2, OLED27.5
C1N27: C277.2, OLED28.5
C1N28: C287.2, OLED29.5
C1N29: C297.2, OLED30.5
C1N30: C307.2, OLED31.5
C1N31: C317.2, OLED32.5
C1N32: C327.2, OLED33.5
C1N33: C337.2, OLED34.5
C1N34: C347.2, OLED35.5
C1N35: C357.2, OLED36.5
C1N36: C367.2, OLED37.5
C1N37: C377.2, OLED38.5
C1N38: C387.2, OLED39.5
C1N39: C397.2, OLED40.5
C1N40: C407.2, OLED41.5
C1N41: C417.2, OLED42.5
C1N42: C427.2, OLED43.5
C1N43: C437.2, OLED44.5
C1N44: C447.2, OLED45.5
C1N45: C457.2, OLED46.5
C1N46: C467.2, OLED47.5
C1N47: C477.2, OLED48.5
C1N48: C487.2, OLED49.5
C1N49: C497.2, OLED50.5
C1N50: C507.2, OLED51.5
C1N51: C517.2, OLED52.5
C1N52: C527.2, OLED53.5
C1N53: C537.2, OLED54.5
C1N54: C547.2, OLED55.5
C1N55: C557.2, OLED56.5
C1N56: C567.2, OLED57.5
C1N57: C577.2, OLED58.5
C1N58: C587.2, OLED59.5
C1N59: C597.2, OLED60.5
C1N60: C607.2, OLED61.5
C1N61: C617.2, OLED62.5
C1N62: C627.2, OLED63.5
C1N63: C637.2, OLED64.5
C1P: C6.1, OLED1.4
C1P1: C17.1, OLED2.4
C1P2: C27.1, OLED3.4
C1P3: C37.1, OLED4.4
C1P4: C47.1, OLED5.4
C1P5: C57.1, OLED6.4
C1P6: C67.1, OLED7.4
C1P7: C77.1, OLED8.4
C1P8: C87.1, OLED9.4
C1P9: C97.1, OLED10.4
C1P10: C107.1, OLED11.4
C1P11: C117.1, OLED12.4
C1P12: C127.1, OLED13.4
C1P13: C137.1, OLED14.4
C1P14: C147.1, OLED15.4
C1P15: C157.1, OLED16.4
C1P16: C167.1, OLED17.4
C1P17: C177.1, OLED18.4
C1P18: C187.1, OLED19.4
C1P19: C197.1, OLED20.4
C1P20: C207.1, OLED21.4
C1P21: C217.1, OLED22.4
C1P22: C227.1, OLED23.4
C1P23: C237.1, OLED24.4
C1P24: C247.1, OLED25.4
C1P25: C257.1, OLED26.4
C1P26: C267.1, OLED27.4
C1P27: C277.1, OLED28.4
C1P28: C287.1, OLED29.4
C1P29: C297.1, OLED30.4
C1P30: C307.1, OLED31.4
C1P31: C317.1, OLED32.4
C1P32: C327.1, OLED33.4
C1P33: C337.1, OLED34.4
C1P34: C347.1, OLED35.4
C1P35: C357.1, OLED36.4
C1P36: C367.1, OLED37.4
C1P37: C377.1, OLED38.4
C1P38: C387.1, OLED39.4
C1P39: C397.1, OLED40.4
C1P40: C407.1, OLED41.4
C1P41: C417.1, OLED42.4
C1P42: C427.1, OLED43.4
C1P43: C437.1, OLED44.4
C1P44: C447.1, OLED45.4
C1P45: C457.1, OLED46.4
C1P46: C467.1, OLED47.4
C1P47: C477.1, OLED48.4
C1P48: C487.1, OLED49.4
C1P49: C497.1, OLED50.4
C1P50: C507.1, OLED51.4
C1P51: C517.1, OLED52.4
C1P52: C527.1, OLED53.4
C1P53: C537.1, OLED54.4
C1P54: C547.1, OLED55.4
C1P55: C557.1, OLED56.4
C1P56: C567.1, OLED57.4
C1P57: C577.1, OLED58.4
C1P58: C587.1, OLED59.4
C1P59: C597.1, OLED60.4
C1P60: C607.1, OLED61.4
C1P61: C617.1, OLED62.4
C1P62: C627.1, OLED63.4
C1P63: C637.1, OLED64.4
C2N: C5.2, OLED1.3
C2N1: C16.2, OLED2.3
C2N2: C26.2, OLED3.3
C2N3: C36.2, OLED4.3
C2N4: C46.2, OLED5.3
C2N5: C56.2, OLED6.3
C2N6: C66.2, OLED7.3
C2N7: C76.2, OLED8.3
C2N8: C86.2, OLED9.3
C2N9: C96.2, OLED10.3
C2N10: C106.2, OLED11.3
C2N11: C116.2, OLED12.3
C2N12: C126.2, OLED13.3
C2N13: C136.2, OLED14.3
C2N14: C146.2, OLED15.3
C2N15: C156.2, OLED16.3
C2N16: C166.2, OLED17.3
C2N17: C176.2, OLED18.3
C2N18: C186.2, OLED19.3
C2N19: C196.2, OLED20.3
C2N20: C206.2, OLED21.3
C2N21: C216.2, OLED22.3
C2N22: C226.2, OLED23.3
C2N23: C236.2, OLED24.3
C2N24: C246.2, OLED25.3
C2N25: C256.2, OLED26.3
C2N26: C266.2, OLED27.3
C2N27: C276.2, OLED28.3
C2N28: C286.2, OLED29.3
C2N29: C296.2, OLED30.3
C2N30: C306.2, OLED31.3
C2N31: C316.2, OLED32.3
C2N32: C326.2, OLED33.3
C2N33: C336.2, OLED34.3
C2N34: C346.2, OLED35.3
C2N35: C356.2, OLED36.3
C2N36: C366.2, OLED37.3
C2N37: C376.2, OLED38.3
C2N38: C386.2, OLED39.3
C2N39: C396.2, OLED40.3
C2N40: C406.2, OLED41.3
C2N41: C416.2, OLED42.3
C2N42: C426.2, OLED43.3
C2N43: C436.2, OLED44.3
C2N44: C446.2, OLED45.3
C2N45: C456.2, OLED46.3
C2N46: C466.2, OLED47.3
C2N47: C476.2, OLED48.3
C2N48: C486.2, OLED49.3
C2N49: C496.2, OLED50.3
C2N50: C506.2, OLED51.3
C2N51: C516.2, OLED52.3
C2N52: C526.2, OLED53.3
C2N53: C536.2, OLED54.3
C2N54: C546.2, OLED55.3
C2N55: C556.2, OLED56.3
C2N56: C566.2, OLED57.3
C2N57: C576.2, OLED58.3
C2N58: C586.2, OLED59.3
C2N59: C596.2, OLED60.3
C2N60: C606.2, OLED61.3
C2N61: C616.2, OLED62.3
C2N62: C626.2, OLED63.3
C2N63: C636.2, OLED64.3
C2P: C5.1, OLED1.2
C2P1: C16.1, OLED2.2
C2P2: C26.1, OLED3.2
C2P3: C36.1, OLED4.2
C2P4: C46.1, OLED5.2
C2P5: C56.1, OLED6.2
C2P6: C66.1, OLED7.2
C2P7: C76.1, OLED8.2
C2P8: C86.1, OLED9.2
C2P9: C96.1, OLED10.2
C2P10: C106.1, OLED11.2
C2P11: C116.1, OLED12.2
C2P12: C126.1, OLED13.2
C2P13: C136.1, OLED14.2
C2P14: C146.1, OLED15.2
C2P15: C156.1, OLED16.2
C2P16: C166.1, OLED17.2
C2P17: C176.1, OLED18.2
C2P18: C186.1, OLED19.2
C2P19: C196.1, OLED20.2
C2P20: C206.1, OLED21.2
C2P21: C216.1, OLED22.2
C2P22: C226.1, OLED23.2
C2P23: C236.1, OLED24.2
C2P24: C246.1, OLED25.2
C2P25: C256.1, OLED26.2
C2P26: C266.1, OLED27.2
C2P27: C276.1, OLED28.2
C2P28: C286.1, OLED29.2
C2P29: C296.1, OLED30.2
C2P30: C306.1, OLED31.2
C2P31: C316.1, OLED32.2
C2P32: C326.1, OLED33.2
C2P33: C336.1, OLED34.2
C2P34: C346.1, OLED35.2
C2P35: C356.1, OLED36.2
C2P36: C366.1, OLED37.2
C2P37: C376.1, OLED38.2
C2P38: C386.1, OLED39.2
C2P39: C396.1, OLED40.2
C2P40: C406.1, OLED41.2
C2P41: C416.1, OLED42.2
C2P42: C426.1, OLED43.2
C2P43: C436.1, OLED44.2
C2P44: C446.1, OLED45.2
C2P45: C456.1, OLED46.2
C2P46: C466.1, OLED47.2
C2P47: C476.1, OLED48.2
C2P48: C486.1, OLED49.2
C2P49: C496.1, OLED50.2
C2P50: C506.1, OLED51.2
C2P51: C516.1, OLED52.2
C2P52: C526.1, OLED53.2
C2P53: C536.1, OLED54.2
C2P54: C546.1, OLED55.2
C2P55: C556.1, OLED56.2
C2P56: C566.1, OLED57.2
C2P57: C576.1, OLED58.2
C2P58: C586.1, OLED59.2
C2P59: C596.1, OLED60.2
C2P60: C606.1, OLED61.2
C2P61: C616.1, OLED62.2
C2P62: C626.1, OLED63.2
C2P63: C636.1, OLED64.2
D1: J3.11, U6.32
D2: J2.11, U3.32
D3: J2.12, U3.1
D4: J3.12, U6.1
D4/3.3V_EN: U1.3, U3.2
D4/3.3V_EN1: U4.3, U6.2
D4/3.3V_EN2: U7.3, U9.2
D4/3.3V_EN3: U10.3, U12.2
D4/3.3V_EN4: U13.3, U15.2
D4/3.3V_EN5: U16.3, U18.2
D4/3.3V_EN6: U19.3, U21.2
D4/3.3V_EN7: U22.3, U24.2
D4/3.3V_EN8: U25.3, U27.2
D4/3.3V_EN9: U28.3, U30.2
D4/3.3V_EN10: U31.3, U33.2
D4/3.3V_EN11: U34.3, U36.2
D4/3.3V_EN12: U37.3, U39.2
D4/3.3V_EN13: U40.3, U42.2
D4/3.3V_EN14: U43.3, U45.2
D4/3.3V_EN15: U46.3, U48.2
D4/3.3V_EN16: U49.3, U51.2
D4/3.3V_EN17: U52.3, U54.2
D4/3.3V_EN18: U55.3, U57.2
D4/3.3V_EN19: U58.3, U60.2
D4/3.3V_EN20: U61.3, U63.2
D4/3.3V_EN21: U64.3, U66.2
D4/3.3V_EN22: U67.3, U69.2
D4/3.3V_EN23: U70.3, U72.2
D4/3.3V_EN24: U73.3, U75.2
D4/3.3V_EN25: U76.3, U78.2
D4/3.3V_EN26: U79.3, U81.2
D4/3.3V_EN27: U82.3, U84.2
D4/3.3V_EN28: U85.3, U87.2
D4/3.3V_EN29: U88.3, U90.2
D4/3.3V_EN30: U91.3, U93.2
D4/3.3V_EN31: U94.3, U96.2
D4/3.3V_EN32: U97.3, U99.2
D4/3.3V_EN33: U100.3, U102.2
D4/3.3V_EN34: U103.3, U105.2
D4/3.3V_EN35: U106.3, U108.2
D4/3.3V_EN36: U109.3, U111.2
D4/3.3V_EN37: U112.3, U114.2
D4/3.3V_EN38: U115.3, U117.2
D4/3.3V_EN39: U118.3, U120.2
D4/3.3V_EN40: U121.3, U123.2
D4/3.3V_EN41: U124.3, U126.2
D4/3.3V_EN42: U127.3, U129.2
D4/3.3V_EN43: U130.3, U132.2
D4/3.3V_EN44: U133.3, U135.2
D4/3.3V_EN45: U136.3, U138.2
D4/3.3V_EN46: U139.3, U141.2
D4/3.3V_EN47: U142.3, U144.2
D4/3.3V_EN48: U145.3, U147.2
D4/3.3V_EN49: U148.3, U150.2
D4/3.3V_EN50: U151.3, U153.2
D4/3.3V_EN51: U154.3, U156.2
D4/3.3V_EN52: U157.3, U159.2
D4/3.3V_EN53: U160.3, U162.2
D4/3.3V_EN54: U163.3, U165.2
D4/3.3V_EN55: U166.3, U168.2
D4/3.3V_EN56: U169.3, U171.2
D4/3.3V_EN57: U172.3, U174.2
D4/3.3V_EN58: U175.3, U177.2
D4/3.3V_EN59: U178.3, U180.2
D4/3.3V_EN60: U181.3, U183.2
D4/3.3V_EN61: U184.3, U186.2
D4/3.3V_EN62: U187.3, U189.2
D4/3.3V_EN63: U190.3, U192.2
D5: J2.13, U3.9
D6: J2.14, U3.10
D7: J3.13, U6.9
D7/!RESET!: OLED1.12, U3.11
D7/!RESET!1: OLED2.12, U6.11
D7/!RESET!2: OLED3.12, U9.11
D7/!RESET!3: OLED4.12, U12.11
D7/!RESET!4: OLED5.12, U15.11
D7/!RESET!5: OLED6.12, U18.11
D7/!RESET!6: OLED7.12, U21.11
D7/!RESET!7: OLED8.12, U24.11
D7/!RESET!8: OLED9.12, U27.11
D7/!RESET!9: OLED10.12, U30.11
D7/!RESET!10: OLED11.12, U33.11
D7/!RESET!11: OLED12.12, U36.11
D7/!RESET!12: OLED13.12, U39.11
D7/!RESET!13: OLED14.12, U42.11
D7/!RESET!14: OLED15.12, U45.11
D7/!RESET!15: OLED16.12, U48.11
D7/!RESET!16: OLED17.12, U51.11
D7/!RESET!17: OLED18.12, U54.11
D7/!RESET!18: OLED19.12, U57.11
D7/!RESET!19: OLED20.12, U60.11
D7/!RESET!20: OLED21.12, U63.11
D7/!RESET!21: OLED22.12, U66.11
D7/!RESET!22: OLED23.12, U69.11
D7/!RESET!23: OLED24.12, U72.11
D7/!RESET!24: OLED25.12, U75.11
D7/!RESET!25: OLED26.12, U78.11
D7/!RESET!26: OLED27.12, U81.11
D7/!RESET!27: OLED28.12, U84.11
D7/!RESET!28: OLED29.12, U87.11
D7/!RESET!29: OLED30.12, U90.11
D7/!RESET!30: OLED31.12, U93.11
D7/!RESET!31: OLED32.12, U96.11
D7/!RESET!32: OLED33.12, U99.11
D7/!RESET!33: OLED34.12, U102.11
D7/!RESET!34: OLED35.12, U105.11
D7/!RESET!35: OLED36.12, U108.11
D7/!RESET!36: OLED37.12, U111.11
D7/!RESET!37: OLED38.12, U114.11
D7/!RESET!38: OLED39.12, U117.11
D7/!RESET!39: OLED40.12, U120.11
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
